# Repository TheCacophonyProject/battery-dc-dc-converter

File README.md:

# battery-dc-dc-converter
Designed to step down the voltage from a scooter battery to 12V

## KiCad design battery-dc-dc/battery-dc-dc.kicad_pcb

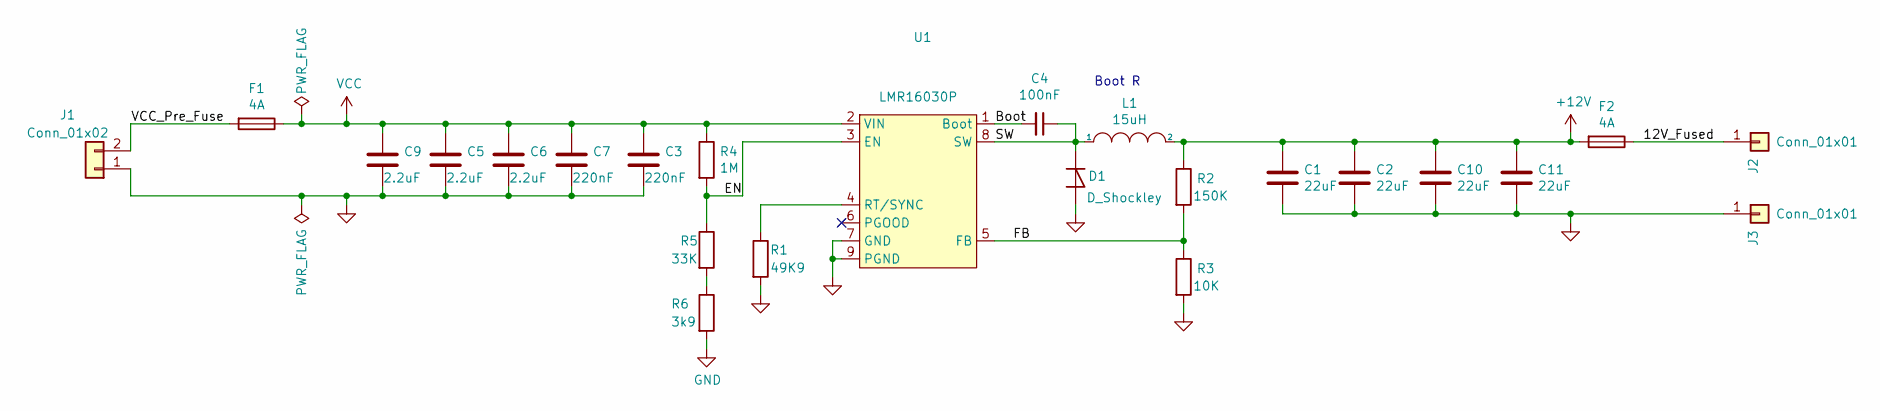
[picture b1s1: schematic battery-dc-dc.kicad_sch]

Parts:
C1, C2, C10, C11: 22uF; C_0805_2012Metric; LCSC C602037
C3, C7: 220nF; C_0805_2012Metric; LCSC C513710
C4: 100nF; C_0603_1608Metric; LCSC C14663
C5, C6, C9: 2.2uF; C_1210_3225Metric; LCSC C55151
D1: D_Shockley; D_SMA; LCSC C22452
F1, F2: 4A; Fuse_1206_3216Metric_Pad1.42x1.75mm_HandSolder; LCSC C136349
J1: Conn_01x02; xt60pw-m; LCSC C98732
J2, J3: Conn_01x01; hole-pad
L1: 15uH; SWRH1207B; LCSC C115137
R1: 49K9; R_0603_1608Metric; LCSC C23184
R2: 150K; R_0603_1608Metric; LCSC C326734
R3: 10K; R_0603_1608Metric; LCSC C25804
R4: 1M; R_0603_1608Metric; LCSC C22935
R5: 33K; R_0603_1608Metric; LCSC C4216
R6: 3k9; R_0603_1608Metric; LCSC C23018
U1: LMR16030P; TI_SO-PowerPAD-8; LCSC C90665

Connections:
+12V: C1.1, C2.1, C10.1, C11.1, F2.2, L1.2, R2.1
/12V_Fused: F2.1, J2.1
/Boot: C4.2, U1.1 (Boot)
/EN: R4.2, R5.1, U1.3 (EN)
/FB: R2.2, R3.1, U1.5 (FB)
/SW: C4.1, D1.1 (K), L1.1, U1.8 (SW)
/VCC_Pre_Fuse: F1.2, J1.2
GND: C1.2, C2.2, C3.2, C5.2, C6.2, C7.2, C9.2, C10.2, C11.2, D1.2 (A), J1.1, J3.1, R1.2, R3.2, R6.2, U1.7 (GND), U1.9 (PGND)
unnamed: R5.2, R6.1
unnamed: R1.1, U1.4 (RT/SYNC)
VCC: C3.1, C5.1, C6.1, C7.1, C9.1, F1.1, R4.1, U1.2 (VIN)

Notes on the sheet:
Boot R

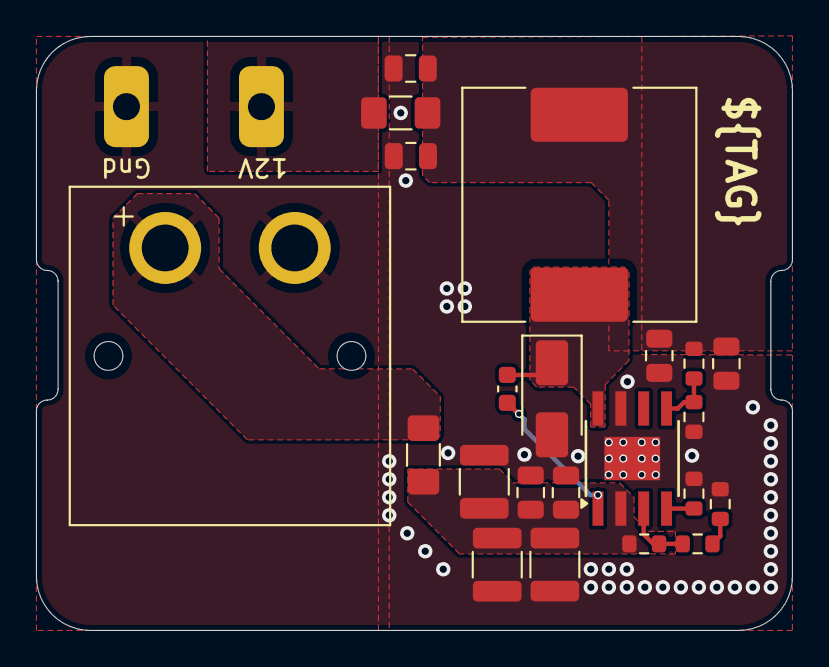
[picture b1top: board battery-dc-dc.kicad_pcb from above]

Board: 4 copper layers, 42.0 x 33.0 mm, 24 parts (0 on the bottom side), 11 nets.

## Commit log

2020-09-11 Add gitignore file
2020-09-11 Add fabrication-output folder
2020-09-11 version 0.1
2020-09-11 Small tidyup of filled zones
2020-11-16 Added fuses
2020-11-19 Added low voltage protection
2020-11-22 Added panelized layout
2021-02-24 Updateed power pads, on/off resistors.
2021-03-16 Panalized PCBs
2021-03-16 Added recessed nibbles
2021-10-10 Improved EMI
2021-10-10 Added lmr16020
2021-10-10 Added dc-dc v0.2 text
2021-10-11 Order v0.2
2021-11-08 Put power plug on same side
2024-11-13 panelize WIP
2024-11-13 Tidy up
2024-11-13 0.4.0 release
